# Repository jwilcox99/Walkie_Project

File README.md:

Repository for collaboration, notes, and resources surrounding our Walkie Talkie Project.

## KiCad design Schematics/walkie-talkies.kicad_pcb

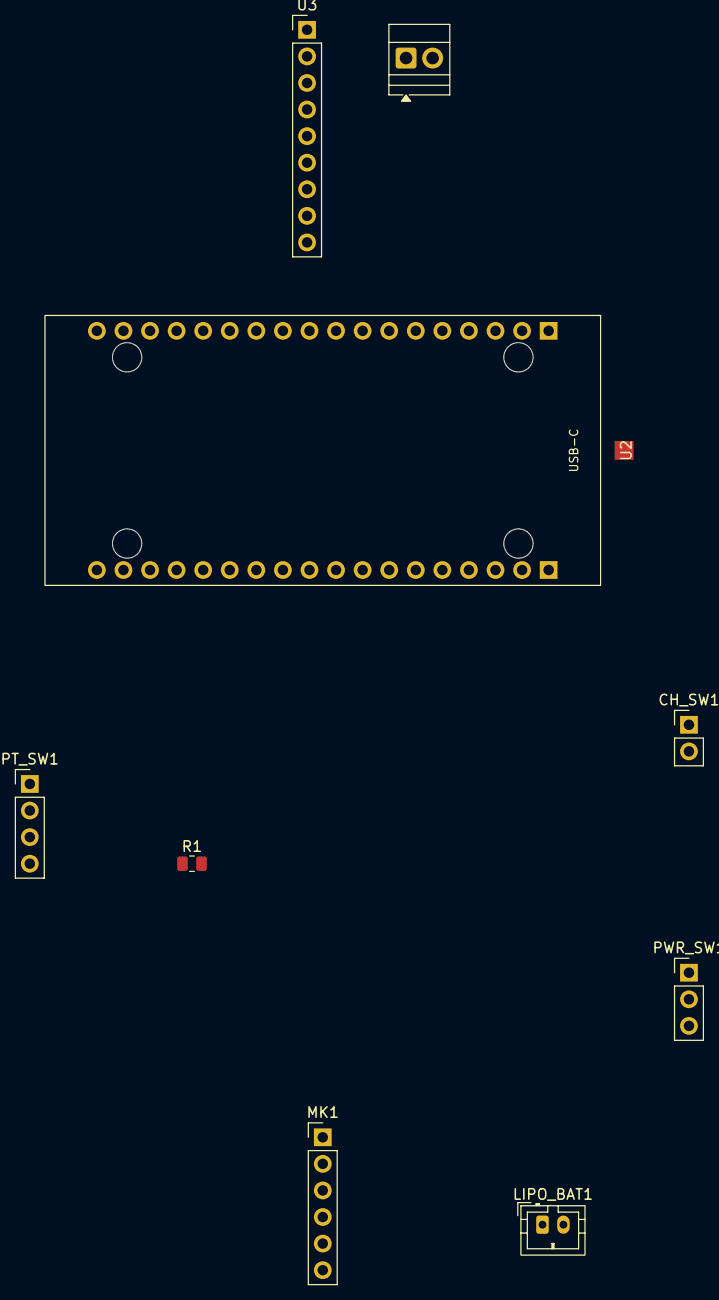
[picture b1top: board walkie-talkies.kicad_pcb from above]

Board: 2 copper layers, 9 parts (0 on the bottom side), 15 nets, no tracks yet.

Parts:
CH_SW1: SW_Push; PinHeader_1x02_P2.54mm_Vertical
LIPO_BAT1: Battery_Cell; JST_PH_B2B-PH-K_1x02_P2.00mm_Vertical
LS1: Speaker; TerminalBlock_Xinya_XY308-2.54-2P_1x02_P2.54mm_Horizontal
MK1: Adafruit_ICS43434_Breakout; PinHeader_1x06_P2.54mm_Vertical
PT_SW1: SW_Push_LED; PinHeader_1x04_P2.54mm_Vertical
PWR_SW1: SW_SPDT; PinHeader_1x03_P2.54mm_Vertical
R1: 1k ohm; R_0805_2012Metric
U2: Heltec_WiFi_LoRa_32_V4_Socket_SymbolNumbered
U3: Adafruit_MAX98357A_Breakout; PinHeader_1x09_P2.54mm_Vertical

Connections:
/CH_SW: CH_SW1.1, U2.5 (GPIO5)
/I2S_BCLK: MK1.4 (BCLK), U3.6 (BCLK)
/I2S_MIC_DATA: MK1.6 (DOUT), U2.33 (GPIO33)
/I2S_SPK_DATA: U2.34 (GPIO34), U3.5 (DIN)
/I2S_WS: MK1.5 (LRCL), U3.7 (LRC)
/NO_CONNECT: PWR_SW1.3 (C), U3.4 (GAIN)
/PTT_LED: PT_SW1.3 (K), U2.6 (GPIO6)
/PTT_SW: PT_SW1.1, U2.4 (GPIO4)
/PWR_SW: PWR_SW1.2 (B), U2.7 (GPIO7)
/VBAT: LIPO_BAT1.1 (+), U2.VBAT
/VE: MK1.1 (3V), R1.1, U2.VE, U3.1 (VDD), U3.3 (SD_MODE)
GND: CH_SW1.2, LIPO_BAT1.2 (-), MK1.2 (GND), MK1.3 (SEL), PT_SW1.2, PWR_SW1.1 (A), U2.GND, U3.2 (GND)
unnamed: PT_SW1.4 (A), R1.2
unnamed: LS1.2, U3.8 (VO+)
unnamed: LS1.1, U3.9 (VO-)

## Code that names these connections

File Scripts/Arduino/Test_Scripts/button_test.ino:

// CXS Walkie Button Test - Heltec WiFi LoRa 32 V4
// Buttons use internal pullups: pressed = LOW

#define PIN_PTT_SW   4
#define PIN_CH_SW    1
#define PIN_PTT_LED  6
#define PIN_PWR_SW   7   // optional test input if wired

bool lastPtt = HIGH;
bool lastCh  = HIGH;
bool lastPwr = HIGH;

unsigned long lastPrint = 0;

void setup() {
  Serial.begin(115200);
  delay(1000);

  pinMode(PIN_PTT_SW, INPUT_PULLUP);
  pinMode(PIN_CH_SW, INPUT_PULLUP);
  pinMode(PIN_PWR_SW, INPUT_PULLUP);

  pinMode(PIN_PTT_LED, OUTPUT);
  digitalWrite(PIN_PTT_LED, LOW);

  Serial.println();
  Serial.println("=== CXS Walkie Button Test ===");
  Serial.println("PTT: GPIO4");
  Serial.println("CH:  GPIO5");
  Serial.println("LED: GPIO6");
  Serial.println("PWR: GPIO7");
  Serial.println("Pressed = LOW");
}

void loop() {
  bool ptt = digitalRead(PIN_PTT_SW);
  bool ch  = digitalRead(PIN_CH_SW);
  bool pwr = digitalRead(PIN_PWR_SW);

  // LED follows PTT button
  digitalWrite(PIN_PTT_LED, ptt == LOW ? HIGH : LOW);

  if (ptt != lastPtt) {
    Serial.print("PTT ");
    Serial.println(ptt == LOW ? "PRESSED" : "released");
    lastPtt = ptt;
    delay(30); // simple debounce
  }

  if (ch != lastCh) {
    Serial.print("CHANNEL ");
    Serial.println(ch == LOW ? "PRESSED" : "released");
    lastCh = ch;
    delay(30);
  }

  if (pwr != lastPwr) {
    Serial.print("POWER SWITCH ");
    Serial.println(pwr == LOW ? "ON/LOW" : "OFF/HIGH");
    lastPwr = pwr;
    delay(30);
  }

  // Heartbeat every 2 sec so you know firmware is alive
  if (millis() - lastPrint > 2000) {
    lastPrint = millis();
    Serial.print("State | PTT=");
    Serial.print(ptt == LOW ? "DOWN" : "UP");
    Serial.print(" CH=");
    Serial.print(ch == LOW ? "DOWN" : "UP");
    Serial.print(" PWR=");
    Serial.println(pwr == LOW ? "LOW" : "HIGH");
  }
}

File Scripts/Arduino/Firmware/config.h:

#pragma once

#define FW_VERSION "v0.3"

#define VEXT_CTRL     36

#define CH_PIN        1
#define PTT_PIN       4
#define PTT_LED_PIN   6
#define PWR_SW_PIN    7

#define I2S_BCLK      46
#define I2S_WS        47
#define I2S_MIC_DATA  33 //Update based on Prototype Josh=33 Snake=35
#define I2S_SPK_DATA  34

#define SAMPLE_RATE          16000
#define SAMPLES_PER_PACKET   80
#define VOLUME_BOOST         3

#define MAX_TALK_GROUPS      5
#define LONG_PRESS_MS        800
#define VERY_LONG_PRESS_MS   2500
#define DEBOUNCE_MS          40

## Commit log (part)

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2026-06-27 Create Feedback Form
2026-06-27 Rename Notes, Updates, and To Do Items.doc to Notes, Updates, and To Do Items
2026-06-30 Create test
